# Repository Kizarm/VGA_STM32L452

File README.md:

# VGA_STM32L452 V2

## Motivace
Začaly se mi tu hromadit monitory VGA s rozměrem 4:3, tak jsem přemýšlel jak je využít.
Zkusil jsem generovat monochromatický signál na Nucleo kitu, osazeném STM32L452. Je to
dost na hraně, pro výstup je použito SPI pomocí DMA, časování je však natolik kritické,
že to funguje jen když je osazen krystal a kód běží z RAM. Ve verzi 2 byl vytvořen vlastní
hardware, protože ty dráty na kitu ve spojení s rychlými SPI sběrnicemi nedělají dobrotu.
V sekci hardware je tedy schema a celý návrh desky, včetně dat pro výrobu - skutečně
je to podle toho vyrobeno a dá se to poměrně primitivními prostředky osadit.

Pro ladění (defaultní stav) je v procesoru nahrán do flash krátký kousek kódu z adresáře
base-ram. Vlastní kód je pak nahráván do RAM, odkud také běží. Je to jednoduchý hack,
který umožňuje ladit v RAM a nemusí se čarovat s BOOT options. I tak kód běží celý z RAM, tj. musí se tam vejít.
Zkoušel jsem dostat do RAM jen kritické části, ale příliš to nepomohlo, cache flash
asi není dostatečně deterministická a přerušení pak trochu rozmazávají pixely.

## bootloader

Základní firmware, který by měl být nahrán do flash procesoru. Je možné ho trochu konfigurovat zkratovými propojkami,
slouží k tomu piny, vyvedené na konektor P1. Pokud není žádná z propojek osazena, program
funguje základním způsobem - po připojení napájecího napětí se pokusí enumerovat se jako USB MSC,
když se mu to nepovede, zkusí z kořenového adresáře FIRMWARE natáhnout do RAM od adresy 0x2000_0000
první soubor, který v tomto adresáři najde a pokud se mu to podaří, spustí ho. Propojky modifikují
chování zhruba následujícím způsobem:

* NO_FILE  - nenatáhne soubor do paměti - pro ladění, podobné jako hack base-ram
* NO_USB   - nečeká na enumeraci USB, je tedy možné spustit uživatelský program i když je to připojeno k PC
* NO_WRITE - MSC se chová jako read only zařízení - R/W přístup často zbytečně přepisuje blok 0 (dirty bit)

## PMD85
V tomto adresáři je jednoduchý emulátor PMD85v2A, včetně programů MONITOR2A a BASICGV2A. Je to jen základ,
emulace je založena na kódu z [githubu](https://github.com/mborik/GPMD85Emulator). Ve verzi 2 je přidána
jednotka PMD32 s daty ve SPI flash. To umožnilo přidat bootloader, který když nahrajeme do procesoru,
pak je zařízení schopné pracovat (po připojení k PC) jako USB mass storage device, na SPI flash
se dá vytvořit FAT filesystém příkazem
```
mkfs.vfat -I -v -F 12 -f 1 -r 128 -S 4096 -s 1 -n LOADER /dev/sdX
```
nakopírovat do flash souborovou strukturu PMD32 (př. /PMD85/cpu/image/fil) a do adresáře FIRMWARE dát
vlastní binárku (linkovanou pro běh z RAM). Pokud pak připojíme desku jen na USB napáječ (aby nedošlo k enumeraci USB),
binárka se nabootuje a spustí. Binárka může být třeba i ten voltmetr.
Pro ladění je přidán Qt4/5 projekt devel, který používá stejné soubory cpu jako firmware. Ladit to přímo v tom
ARM čipu není zase taková sranda a co funguje na jedné platformě, funguje zpravidla i na jiné, pokud se to překládá gcc.
Pozn. Ten FAT filesystém a i USB MSC je trochu nestardní, používá délku bloku 4096B (kvůli použití flash - NOR).

## Voltmeter
To je jen taková blbina, ale zajímavě vypadá. Čte to napětí na PA2 a zobrazuje ho

Má to FIR filtr, který napodobí kývání ručičky. Nastavovat tím nějakou veličinu je opravdu
příjemnější než při použití digitálního měřidla.

## TRNG
Protože hardware má vyvedeno USB a procesor obsahuje docela dobrý generátor náhodných
čísel, byla škoda to nějak nevyužít. Popis má vlastní README.md v adresáři TRNG.

## VT100
Textový displej podobný VT100. Escape sekvence jsou dost zjednodušené, stejně tak kódy klávesnice.
Default se to navenek chová jako USB CDC zařízení, ale je možné použít jako vstup/výstup USART,
jehož piny TxD (PA2) a RxD (PA3) jsou vyvedeny na konektor. Provedeme to příkazy
```
make clean
patch -p2 < usart.patch
make
```
Funguje to dobře např. pokud to použijeme jako konzoli v simulaci [historických počítačů](https://github.com/simh/simh),
kde jdou data na konzoli relativně pomalu. Jako konzole linuxu pomocí getty USB CDC dělá neplechu - dat
přichází moc najednou a displej problikává, protože mu vypadne synchonizace. Umravnit to by bylo moc práce.
USART použitelný vcelku je, ale zase - Linux používá i escape sekvence, které nejsou implemetovány. A další
věcí je, že formát obrazovky je jiný než u původního VT100. V podstatě jsem to dělal jen proto,
aby mi v simulaci PDP11 s OS RSX11M běželo RMD. Prostě vzpomínky na svět SMEP. Ono to nezaškodí podívat
se těch pár desítek let zpátky - člověk si uvědomí jak se od té doby zlepšil komfort práce s počítačem.
A zároveň jak málo se změnily základní principy - i tam bylo C-čko, textový editor a příkazová řádka
s nějakým procesorem (možnost skriptování příkazů). RSX11M byl první OS hodný toho jména se kterým jsem
se setkal, měli jsme tu výhodu, že už tenkrát jsme mohli používat originální verzi, kerá se dnes dá sehnat
na Internetu. Jen se tehdy nedalo používat C-čko, většina programů se vytvářela v assembleru, dal se používat
Fortran a Basic. C-čkový překladač nebyl a ten co je pro RSX11M dnes dostupný na webu je stejně primitivní,
ne tak propracovaný jako Fortran. C-čko se prostě začalo rozvíjet až s příchodem UNIXu.

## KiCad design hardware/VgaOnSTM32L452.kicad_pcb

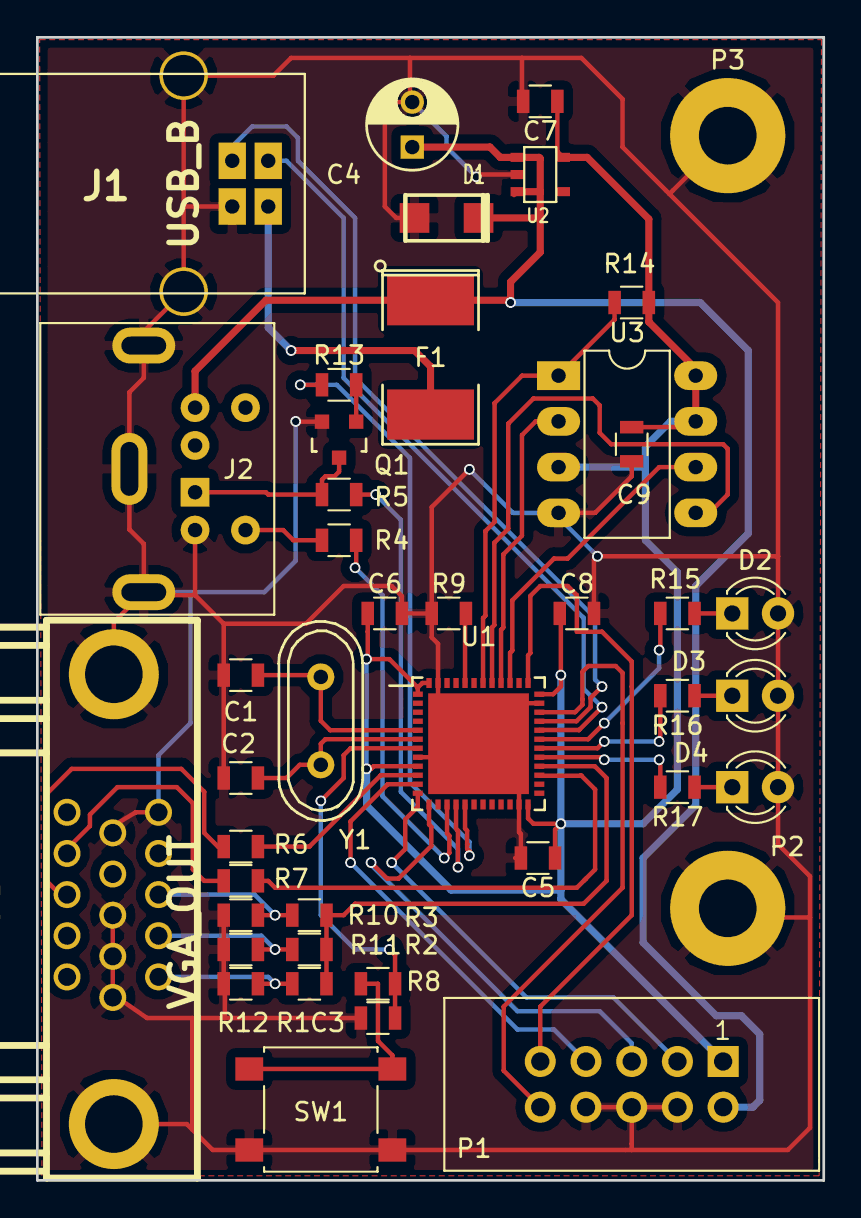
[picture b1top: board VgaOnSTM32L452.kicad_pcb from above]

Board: 2 copper layers, 43.7 x 63.5 mm, 43 parts (0 on the bottom side), 40 nets.

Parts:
C1, C2: 22; R_0805
C3: 22n; R_0805
C4: 100u; C_Radial_D5_L6_P2.5
C5, C6, C7, C8, C9: 220n; R_0805
D1: 5V6; DO_214AC
D2, D3, D4: LED; LED_D3.0mm
F1: Polyfuse; SMD-2112_Pol
J1: USB_B
J2: PS2_KEYBOARD; Connector_Mini-DIN_Female_6Pin_2rows
J3: VGA_OUT; DB15F-VGA
P1: CONN_02X05; IDC_Header_Straight_10pins
P2, P3: PIN; MountingHole_3.2mm_M3_Pad
Q1: BC847; SOT-23
R1, R2, R3, R6, R7: 200; R_0805
R4, R5, R13, R14: 4k7; R_0805
R8, R10, R11, R12, R15, R16, R17: 1k; R_0805
R9: 10k; R_0805
SW1: SW_Push; SW_SPST_B3S-1000
U1: STM32L452CUx; TQFP-48-1EP_7x7mm_Pitch0.5mm
U2: TPS73033DBV; SOT23-5
U3: SPI_NOR; DIP-8_W7.62mm_LongPads
Y1: 8MHz; Crystal_HC49-U_Vertical

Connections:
+5V: C4.1, D1.2, F1.1, J2.4, P1.2, U2.1, U2.3
/BLUE: J3.3, R3.1, R10.2
/CLK: J2.5, R4.2
/DATA: J2.1, Q1.3, R5.2
/GREEN: J3.2, R2.1, R11.2
/HSYNC: J3.13, R6.2
/RED: J3.1, R1.1, R12.2
/VBUS: F1.2, J1.1
/VSYNC: J3.14, R7.2
FCS: R14.2, U1.42, U3.1
GND: C1.2, C2.2, C3.2, C4.2, C5.2, C6.2, C7.2, C8.2, C9.2, D1.1, D2.2, D3.2, D4.2, J1.4, J1.5, J1.6, J2.3, J2.7, J3.0, J3.5, J3.6, J3.7, J3.8, J3.10, P1.4, P1.6, P1.8, P2.1, P3.1, Q1.2, R9.1, R10.1, R11.1, R12.1, SW1.1, U1.8, U1.23, U1.35, U1.47, U1.49, U2.2, U3.4
LED1: R15.2, U1.31
LED2: R16.2, U1.30
LED3: R17.2, U1.29
MISO: U1.40, U3.2
MOSI: U1.41, U3.5
unnamed: D2.1, R15.1
unnamed: D3.1, R16.1
unnamed: D4.1, R17.1
unnamed: Q1.1, R13.2
unnamed: R8.2, SW1.2
unnamed: R9.2, U1.44
PA0: R6.1, U1.10
PA1: P1.7, U1.11
PA5: R4.1, U1.15
PA6: R5.1, U1.16
PA7: R13.1, U1.17
PA11: J1.2, U1.32
PA12: J1.3, U1.33
PB14: R7.1, U1.27
PB15: R1.2, R2.2, R3.2, U1.28
PH0: C1.1, U1.5, Y1.1
PH1: C2.1, U1.6, Y1.2
RESET: C3.1, R8.1, U1.7
RX: P1.5, U1.13
SCK: U1.39, U3.6
SWCLK: P1.9, U1.37
SWDIO: P1.10, U1.34
TX: P1.3, U1.12
VDD: C5.1, C6.1, C7.1, C8.1, C9.1, P1.1, R14.1, U1.1, U1.9, U1.24, U1.36, U1.48, U2.5, U3.3, U3.7, U3.8

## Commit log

2021-01-10 add code
2021-01-10 dodelano README
2021-01-10 opraveny preklepy
2021-01-10 opraveno propojeni
2021-02-01 verze 2
2021-02-03 verze pro Kicad 5
2021-02-03 castecne vycisteno
2021-02-07 uprava bootloader
2021-02-12 add TRNG
2021-02-12 upraven TRNG
2021-02-15 add VT100
2021-02-18 opraveno samplovani ADC
2021-03-03 add fractals
2021-07-10 chyba vt100
2022-02-01 add sudoku
2022-02-01 oprava README
2022-02-02 pridany klavesy end a delete
2022-07-12 prechod na UBUNTU 20.04, jina verze newlib a gcc
2022-07-16 wchar_t -> char16_t
2023-01-19 sudoku - wasm without emscripten
2023-06-15 drobna uprava bootloader
